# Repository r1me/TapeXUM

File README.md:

# TapeXUM
TapeXUM is a USB device that can read and write to cassettes of Commodore 16/64/VIC-20 (read and write) and ZX Spectrum (read only) format. It requires a Commodore datasette connected to it. This project is based on ZoomTape by Arnd Menge, a great idea and originally a part of OpenCBM package. TapeXUM uses Arduino Pro Micro and through hole components so it's a DIY friendly design.  
Huge thanks to Data/Tropyx for creating enclosure design for 3D printing!  

### Changes in software (since ZoomTape)
- modified device firmware to support Arduino Pro Micro
- added ability to continue tape capture even if stopped (before that, read was interrupted once datasette playback had stopped i.e. with Stop button)
- added azimuth adjustment feature (prepare your screwdriver)

### BOM
| Component  | qty |
| ------------- | ------------- |
| Arduino Pro Micro 5V | 1 |
| 1/4W Resistor for LEDs (~1K, depending on your preference) | 2 |
| 1/4W 1K Resistor | 1 |
| 1/2W 1.5k Resistor | 1 |
| 2N3904 Transistor | 1 |
| 2SD880 or 2SD313 Transistor | 1 |
| 3mm LED (i.e. green and red) | 2 |
| 6V8 Zener diode | 1 |
| 1N400x diode | 1 |
| 1uF electrolytic capacitor | 1 |
| 0.1uF electrolytic capacitor | 1 |
| Barrel jack DC connector 2.1/5.5mm or 2.5/5.5mm | 1 |
| 1x3 pin header 2.54mm and a jumper | 1 |
| 9VDC 500mA power supply with DC connector (center positive) | 1 |
| Micro USB cable | 1 |

### Download
Windows 7/10 64-bit libraries and tools: https://github.com/r1me/TapeXUM/releases/download/1.0/xum-installer-x64.zip  
Get PCB's from PCBWay: https://www.pcbway.com/project/shareproject/TapeXUM___Capture_and_write_Commodore_tapes_via_USB_device.html   
Gerber and Kicad files (hardware design): https://github.com/r1me/TapeXUM/tree/main/hardware  
Firmware for Arduino Pro Micro: https://github.com/r1me/TapeXUM/tree/main/firmware  
3D enclosure: https://www.thingiverse.com/thing:4659235  
OpenCBM: https://github.com/r1me/OpenCBM  

### Programming Arduino
`avrdude -p m32u4 -c avr109 -P comX -U flash:w:xum1541-PROMICRO_TAPE-v08.hex`

### License
TapeXUM follows same license for software as OpenCBM. PCB design of TapeXUM is free and shared under CERN OHW v2 (open hardware licence).

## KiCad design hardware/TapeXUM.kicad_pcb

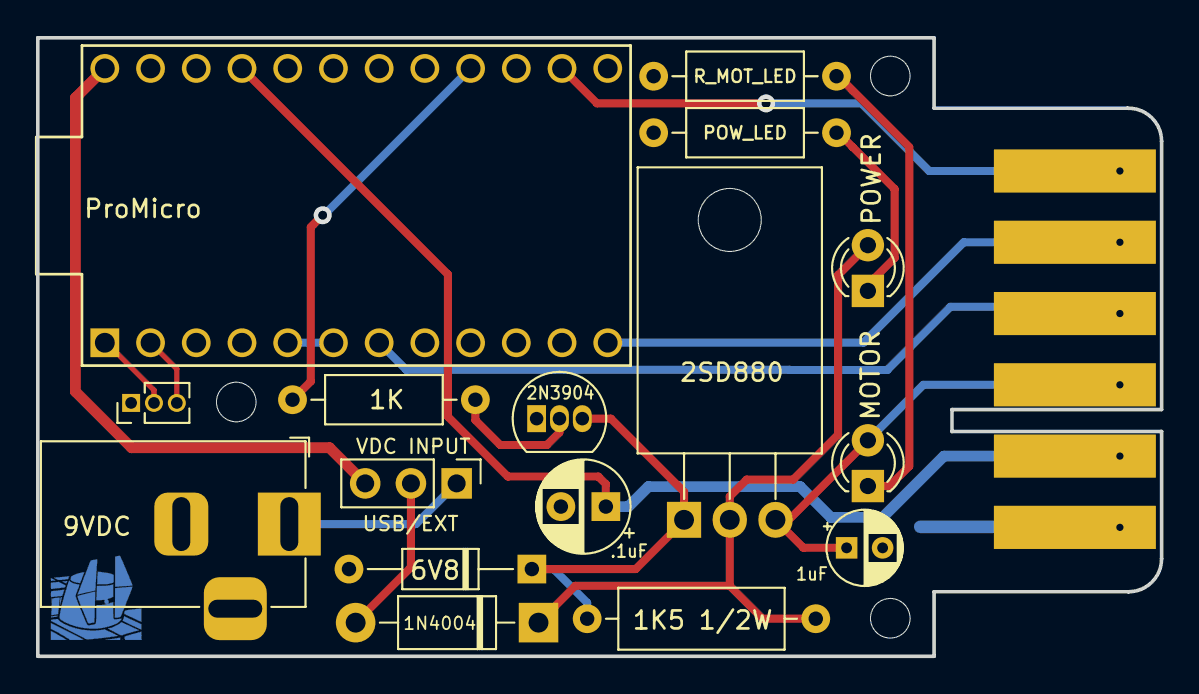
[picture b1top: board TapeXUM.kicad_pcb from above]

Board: 2 copper layers, 62.4 x 34.4 mm, 17 parts (0 on the bottom side), 18 nets.

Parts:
C1: 1uF; CP_Radial_D4.0mm_P2.00mm
C2: .1uF; CP_Radial_D5.0mm_P2.50mm
D1: 1N4004; D_DO-41_SOD81_P10.16mm_Horizontal
D2: MOTOR; LED_D3.0mm
D3: 6V8; D_DO-35_SOD27_P10.16mm_Horizontal
D4: POWER; LED_D3.0mm
J1: Conn_01x06; conn_datasette2
J2: Conn_01x02; BarrelJack_Horizontal
J3: DEBUG; PinHeader_1x03_P1.27mm_Vertical
JP1: VDC INPUT; PinHeader_1x03_P2.54mm_Vertical
Q1: 2SD880; TO-220-3_Horizontal_TabDown
Q2: 2N3904; TO-92_Inline
R1, R4: R; R_Axial_DIN0207_L6.3mm_D2.5mm_P10.16mm_Horizontal
R2: 1K5 1/2W; R_Axial_DIN0309_L9.0mm_D3.2mm_P12.70mm_Horizontal
R3: 330R; R_Axial_DIN0207_L6.3mm_D2.5mm_P10.16mm_Horizontal
U1: ProMicro

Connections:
6VDC: J2.1, JP1.1
+5V: C2.1, J1.2, U1.21
EXT_VDC: D1.2, JP1.2
GND: C1.2, C2.2, D3.2, J1.1, J2.2, J3.1, Q2.1, R1.1, R4.1, U1.3, U1.4, U1.23
MOTOR_CONTROL_PIN: R3.1, U1.16
unnamed: D1.1, D4.2, Q1.2, R2.1
unnamed: D2.1, R1.2
unnamed: D3.1, Q1.1, Q2.3, R2.2
unnamed: D4.1, R4.2
unnamed: Q2.2, R3.2
unnamed: U1.5, U1.6
RAW_5V: JP1.3, U1.24
TAP_MOTOR: C1.1, D2.2, J1.3, Q1.3
TAP_READ: J1.4, U1.7
TAP_SENSE: J1.6, U1.14
TAP_WRITE: J1.5, U1.12
TEST_RX: J3.3, U1.2
TEST_TX: J3.2, U1.1

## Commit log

2020-12-02 Added hardware design in Kicad and gerber files
2020-12-02 Added firmware file
2020-12-02 Added XUM1541/TapeXUM installer source
    Written in Delphi 10.3. Tested in Windows 7 and 10 64-bit
2020-12-02 Add sticker design for 3D enclosure
2020-12-02 Add ZIP file for gerbers
2020-12-06 Add schematics in PDF format
2020-12-29 Added tapfit tool source
    tapfit can be used for azimuth head alignment

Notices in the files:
hardware/TapeXUM.kicad_pcb:
and OpenCBM licensed as GPLv2
